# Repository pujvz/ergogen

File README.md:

# nib

# Part selection
- Keycaps: 3D print
- Choc hotswap (choc spacing)
- Choc switches: 
- MCU (promicro footprint):
  - wired (rp2040): Elite-pi
  - wireless: nice!nano
- Machine pin sockets
- Diodes: IN4148 SOD-123
- 4.7K resistors: ERJ2RKF4701X
- Trackpoint: 

# Ergogen
1. Use Ergogen to generate layout. Complete
2. 3D print plate and insert switches and keycaps. Test ergonomics of layout. Complete
3. Add footprints:
   - reset switch. Complete
   - trrs jack. Complete
   - mcu. Complete
   - trackpoint hole. Complete
   - trackpoint connector (GND, VCC, CLK, DATA, RESET). Complete
   - RESET jumper. Complete
   - mounting holes. Complete

# PCB
- Determine reasonable pin assignments. Complete
- Assign nets. Complete
- Determine cutout area for trackpoint. Complete
- Generate traces. Complete
    - Autorouting with Freerouting. Complete
- Review.

# QMK firmware

# Trackpoint
1. Select trackpoint module. Complete
2. Copy footprint of trackpoint module. Complete
3. Test trackpoint with 1key qmk.

# Case
3D modeling:
- Case
    - Trackpoint mount
    - Tenting
- Palmrest

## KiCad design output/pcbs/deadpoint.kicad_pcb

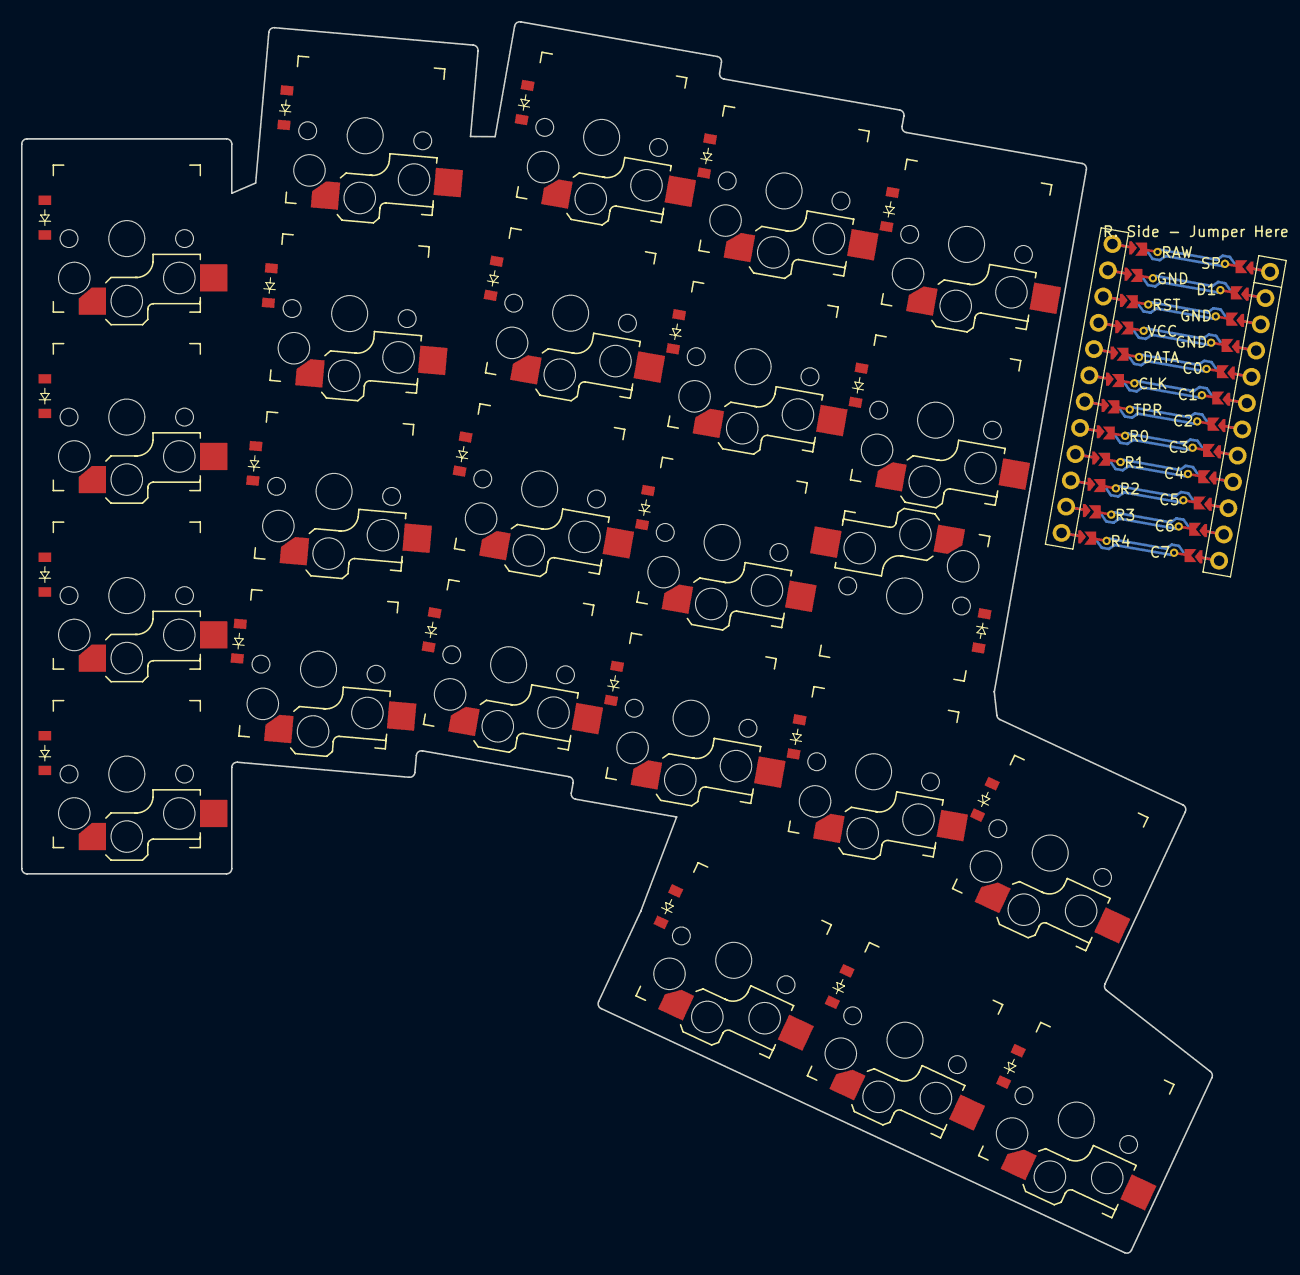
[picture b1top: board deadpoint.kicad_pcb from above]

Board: 2 copper layers, 113.4 x 117.3 mm, 49 parts (0 on the bottom side), 36 nets.

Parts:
D1, D2, D3, D4, D5, D6, D7, D8, D9, D10, D11, D12, D13, D14, D15, D16, D17, D18, D19, D20, D21, D22, D23, D24: ComboDiode
MCU1: nice_nano
S1, S2, S3, S4, S5, S6, S7, S8, S9, S10, S11, S12, S13, S14, S15, S16, S17, S18, S19, S20, S21, S22, S23, S24: PG1350

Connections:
C1: MCU1.119, S1.1, S2.1, S3.1, S4.1
C2: MCU1.118, S5.1, S6.1, S7.1, S8.1
C3: MCU1.117, S9.1, S10.1, S11.1, S12.1
C4: MCU1.116, S13.1, S14.1, S15.1, S16.1, S21.1
C5: MCU1.115, S17.1, S18.1, S19.1, S20.1, S22.1, S23.1
C6: MCU1.114, S24.1
GND: MCU1.2, MCU1.121, MCU1.122
R0: D4.1, D8.1, D12.1, D16.1, D20.1, MCU1.8
R1: D3.1, D7.1, D11.1, D15.1, D19.1, MCU1.9
R2: D2.1, D6.1, D10.1, D14.1, D18.1, MCU1.10
R3: D1.1, D5.1, D9.1, D13.1, D17.1, D23.1, MCU1.11
R4: D21.1, D22.1, D24.1, MCU1.12
base_lower: D22.2, S22.2
base_upper: D23.2, S23.2
extension_lower: D24.2, S24.2
flexion_lower: D21.2, S21.2
index_bottom: D13.2, S13.2
index_home: D14.2, S14.2
index_num: D16.2, S16.2
index_top: D15.2, S15.2
inner_bottom: D17.2, S17.2
inner_home: D18.2, S18.2
inner_num: D20.2, S20.2
inner_top: D19.2, S19.2
middle_bottom: D9.2, S9.2
middle_home: D10.2, S10.2
middle_num: D12.2, S12.2
middle_top: D11.2, S11.2
pinky_bottom: D1.2, S1.2
pinky_home: D2.2, S2.2
pinky_num: D4.2, S4.2
pinky_top: D3.2, S3.2
ring_bottom: D5.2, S5.2
ring_home: D6.2, S6.2
ring_num: D8.2, S8.2
ring_top: D7.2, S7.2

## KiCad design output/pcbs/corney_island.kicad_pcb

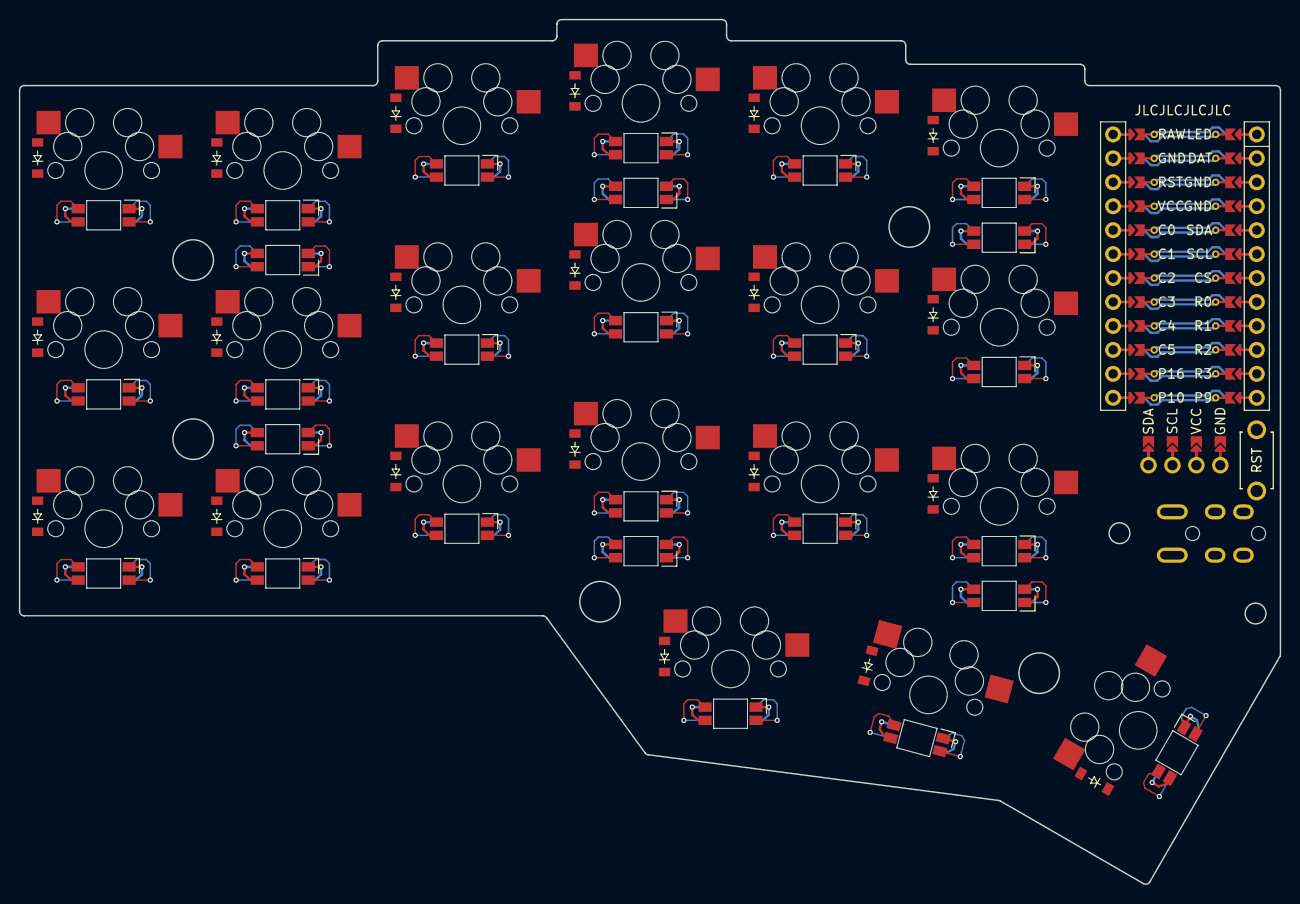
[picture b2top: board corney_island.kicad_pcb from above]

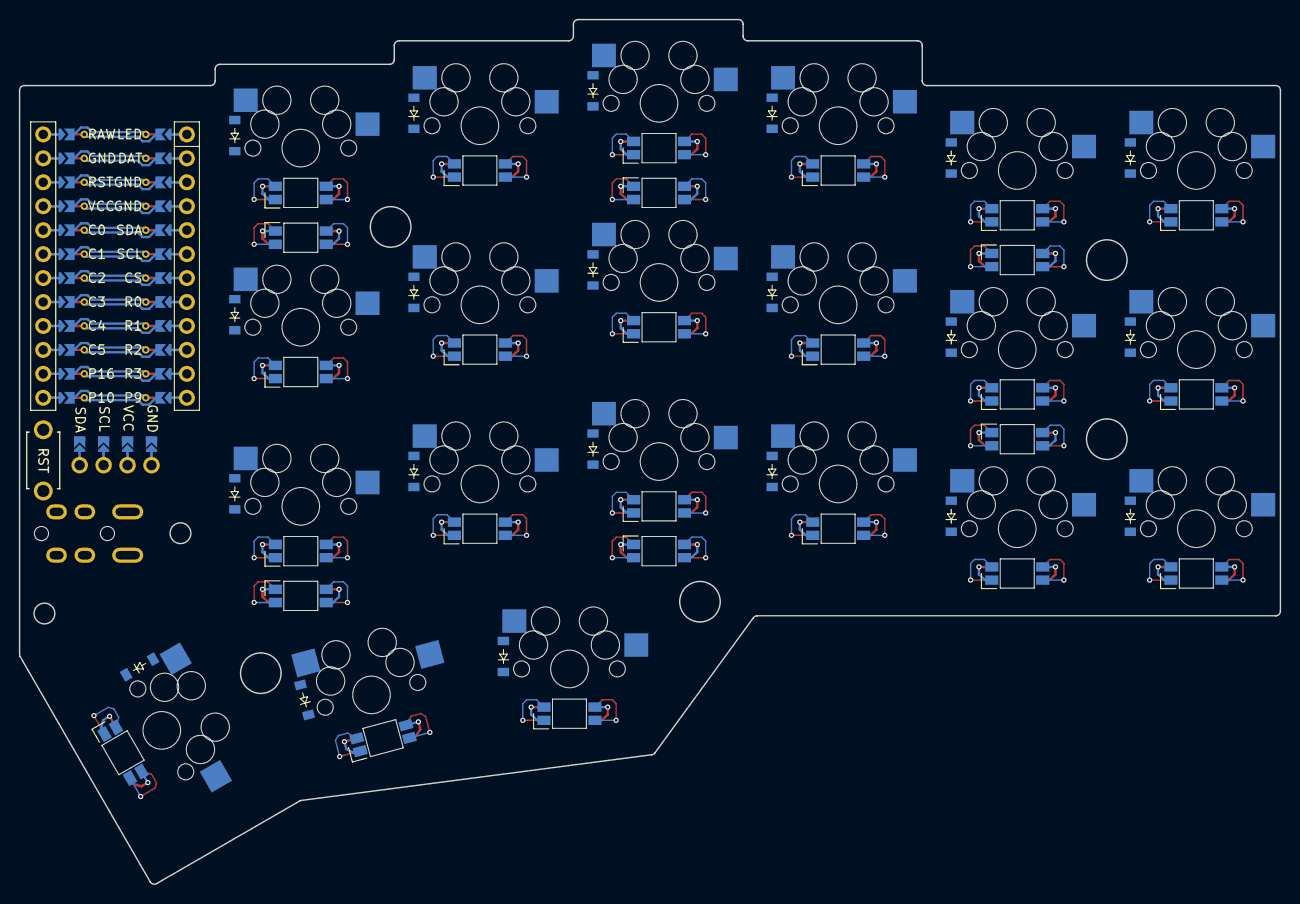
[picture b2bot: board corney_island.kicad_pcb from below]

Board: 2 copper layers, 133.8 x 91.7 mm, 94 parts (48 on the bottom side), 68 nets.

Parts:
B1: Reset (PTS636 SP43 LFS); top-actuated-reset-switch
D1, D2, D3, D4, D5, D6, D7, D8, D9, D10, D11, D12, D13, D14, D15, D16, D17, D18, D19, D20, D21, D22, D23, D24, D25, D26, D27, D28, D29, D30, D31, D32, D33, D34, D35, D36, D37, D38, D39, D40, D41, D42: ComboDiode
DISP1: combo_display
LED1, LED2, LED3, LED4, LED5, LED6, LED7, LED8, LED9, LED10, LED11, LED12, LED13, LED14, LED15, LED16, LED17, LED18, LED19, LED20, LED21: YS-SK6812MINI-E (per-key)
LED22, LED23, LED24, LED25, LED26, LED27: YS-SK6812MINI-E (underglow)
MCU1: nice_nano
S1, S2, S3, S4, S5, S6, S7, S8, S9, S10, S11, S12, S13, S14, S15, S16, S17, S18, S19, S20, S21: MX
TRRS1: TRRS-PJ-320A-dual; TRRS-PJ-320A-dual (reversible, symmetric)

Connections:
C0: MCU1.5, S1.1, S2.1, S3.1
C1: MCU1.6, S4.1, S5.1, S6.1
C2: MCU1.7, S7.1, S8.1, S9.1
C3: MCU1.8, S10.1, S11.1, S12.1, S19.1
C4: MCU1.9, S13.1, S14.1, S15.1, S20.1
C5: MCU1.10, S16.1, S17.1, S18.1, S21.1
DAT: MCU1.123, TRRS1.1
DISP1_1: DISP1.1, DISP1.14, DISP1.24
DISP1_2: DISP1.2, DISP1.13, DISP1.23
DISP1_3: DISP1.3, DISP1.12, DISP1.22
DISP1_4: DISP1.4, DISP1.11, DISP1.21
GND: B1.2, DISP1.31, DISP1.41, LED1.3, LED2.3, LED3.3, LED4.3, LED5.3, LED6.3, LED7.3, LED8.3, LED9.3, LED10.3, LED11.3, LED12.3, LED13.3, LED14.3, LED15.3, LED16.3, LED17.3, LED18.3, LED19.3, LED20.3, LED21.3, LED22.3, LED23.3, LED24.3, LED25.3, LED26.3, LED27.3, MCU1.2, MCU1.121, MCU1.122, TRRS1.2
LED: LED22.4, MCU1.124
LED_1: LED16.4, LED21.2
LED_2: LED16.2, LED17.4
LED_3: LED17.2, LED18.4
LED_4: LED15.4, LED18.2
LED_5: LED14.4, LED15.2
LED_6: LED13.4, LED14.2
LED_7: LED13.2, LED20.4
LED_8: LED19.4, LED20.2
LED_9: LED10.4, LED19.2
LED_10: LED10.2, LED11.4
LED_11: LED11.2, LED12.4
LED_12: LED9.4, LED12.2
LED_13: LED8.4, LED9.2
LED_14: LED7.4, LED8.2
LED_15: LED4.4, LED7.2
LED_16: LED4.2, LED5.4
LED_17: LED5.2, LED6.4
LED_18: LED3.4, LED6.2
LED_19: LED2.4, LED3.2
LED_20: LED1.4, LED2.2
R0: D3.1, D6.1, D9.1, D12.1, D15.1, D18.1, D24.1, D27.1, D30.1, D33.1, D36.1, D39.1, MCU1.117
R1: D2.1, D5.1, D8.1, D11.1, D14.1, D17.1, D23.1, D26.1, D29.1, D32.1, D35.1, D38.1, MCU1.116
R2: D1.1, D4.1, D7.1, D10.1, D13.1, D16.1, D22.1, D25.1, D28.1, D31.1, D34.1, D37.1, MCU1.115
R3: D19.1, D20.1, D21.1, D40.1, D41.1, D42.1, MCU1.114
RST: B1.1, MCU1.3
SCL: DISP1.33, DISP1.43, MCU1.119
SDA: DISP1.34, DISP1.44, MCU1.120
ULED_1: LED22.2, LED23.4
ULED_2: LED23.2, LED24.4
ULED_3: LED24.2, LED25.4
ULED_4: LED25.2, LED26.4
ULED_5: LED26.2, LED27.4
ULED_6: LED21.4, LED27.2
VCC: DISP1.32, DISP1.42, LED1.1, LED2.1, LED3.1, LED4.1, LED5.1, LED6.1, LED7.1, LED8.1, LED9.1, LED10.1, LED11.1, LED12.1, LED13.1, LED14.1, LED15.1, LED16.1, LED17.1, LED18.1, LED19.1, LED20.1, LED21.1, LED22.1, LED23.1, LED24.1, LED25.1, LED26.1, LED27.1, MCU1.4, TRRS1.3
far_home: D21.2, D42.2, S21.2
index_bottom: D13.2, D34.2, S13.2
index_home: D14.2, D35.2, S14.2
index_top: D15.2, D36.2, S15.2
inner_bottom: D16.2, D37.2, S16.2
inner_home: D17.2, D38.2, S17.2
inner_top: D18.2, D39.2, S18.2
mid_home: D20.2, D41.2, S20.2
middle_bottom: D10.2, D31.2, S10.2
middle_home: D11.2, D32.2, S11.2
middle_top: D12.2, D33.2, S12.2
near_home: D19.2, D40.2, S19.2
outer_bottom: D1.2, D22.2, S1.2
outer_home: D2.2, D23.2, S2.2
outer_top: D3.2, D24.2, S3.2
pinky_bottom: D4.2, D25.2, S4.2
pinky_home: D5.2, D26.2, S5.2
pinky_top: D6.2, D27.2, S6.2
ring_bottom: D7.2, D28.2, S7.2
ring_home: D8.2, D29.2, S8.2
ring_top: D9.2, D30.2, S9.2

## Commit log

2023-08-08 first
2023-09-24 added some output
2023-09-24 updated kim submodule
2023-09-27 files
2023-09-27 edit footprints
2023-10-01 edit footprint. rotate matrix_inner_home
2023-10-01 edit mcu footprint, udpate mcu pins in config.yaml. update readme
2023-11-04 lots of changes
2023-11-05 remove unneeded files. update readme. update config
2023-11-26 need to fix data/clock still
2023-12-19 new layout. added pinky splay and increased thumb splay
2023-12-19 adjust splay
